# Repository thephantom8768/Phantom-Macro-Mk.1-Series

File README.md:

# Phantom Macro Mk.1 Series

> A modular, snap-together macropad ecosystem with lateral pogo-pin bus interconnects.

Chain modules side-by-side to expand your desktop workflow—from a compact macro-pad into a full fledge keyboard.

---

## 📌 Project Status

- **Hardware:** Series still in-dev
- **Firmware:** Pad is almost complete but I need to built it to measure the adc. Others are still in-dev
- **Interconnect:** Custom edge-mount 8 pin pogo interface.

---

## ⚡ Features

- **Snap & Chain Topology:** Expand your layout horizontally by mating adjacent modules using edge-mounted pogo connectors.
- **Unified Bus Standard:** Standardized power, ground, and communication rails allow any Mk.1-series compatible module to hot-mate with the system.
- **Flexible Layouts:** Mix and match different form factors (numpads, macro clusters, encoder dials) without rerunning separate USB cables to your host machine.

## ⚠️ Build Warnings

> [!WARNING]
> **DIY Soldering Required:** This is a fully self-assembled project. It is not a plug-and-play kit and requires intermediate soldering experience.

* **Double-Sided Assembly:** Depending on the macro-pad, components might need to be soldered onto **both the top and bottom** of the PCB.

## *Mk.1 Series*

<details>
  <summary><b>🔢 Phantom-Macro-Mk.1 Pad (click here)</b></summary>
  
  ### Macro Mk.1 Pad
  
  #### Schematic

#### PCB Layout

4 Layers PCB

<div style="width: max; height: max; overflow: hidden; display: inline-block;">
  
</div>

| Front (1st layer) | Bottom (4th layer) |
| ----------------- | ------------------ |
|  |  |
|  |  |

#### PCB
| Front | Back |
| ----- | ---- |
|  |  |
|  |  |

#### Case

<table>
  <tbody>
    <tr>
      <td width="50%">
        
      </td>
      <td width="50%">
        
      </td>
    </tr>
    <tr>
      <td width="50%">
        
      </td>
      <td width="50%">
        
      </td>
    </tr>
  </tbody>
</table>

</details>

<details>
  <summary><b>🎹 Phantom-Macro-Mk.1 MIDI (click here)</b></summary>
  
  ### Macro Mk.1 MIDI
  
  #### Schematic

  #### PCB Layout 

  2 Layers PCB

  | Front | Back |
  | ----- | ----- |
  |  |  |
  |  |  |

  #### PCB
  | Front | Back |
  | ----- | ---- |
  |  |  |
  |  |  |

</details>

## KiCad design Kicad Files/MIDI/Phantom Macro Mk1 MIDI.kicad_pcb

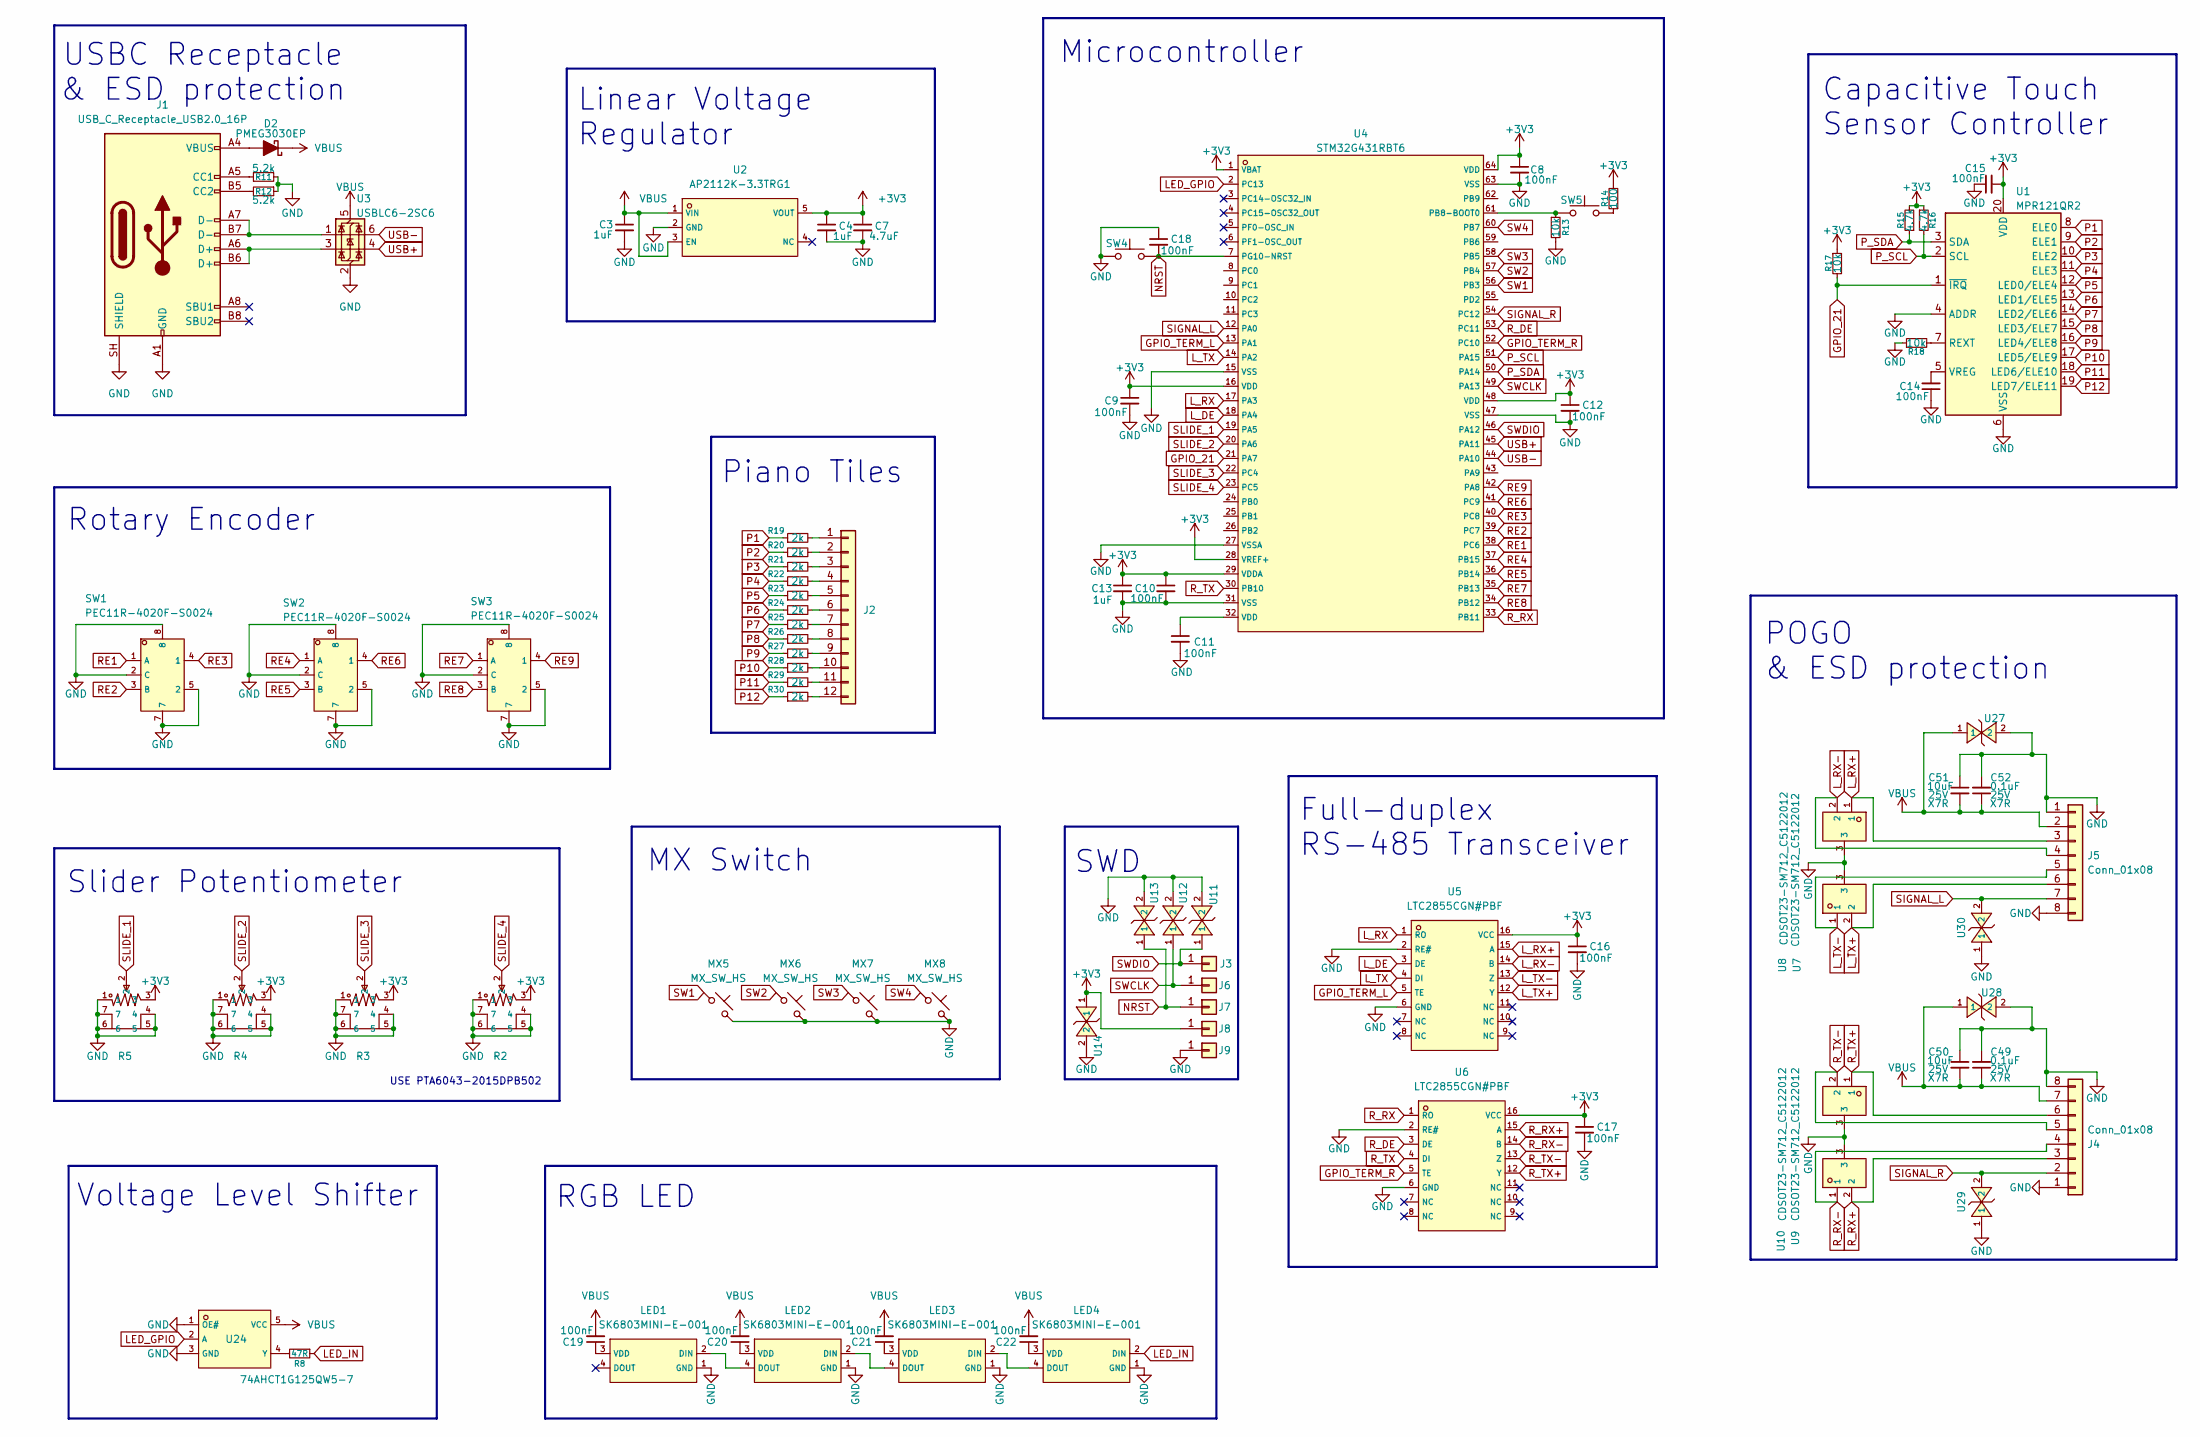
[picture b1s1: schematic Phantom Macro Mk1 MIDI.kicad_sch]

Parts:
C3, C4, C13: 1uF; C_0603_1608Metric_Pad1.08x0.95mm_HandSolder
C7: 4.7uF; C_0805_2012Metric_Pad1.18x1.45mm_HandSolder
C8, C9, C10, C11, C12, C14, C15, C16, C17, C18, C19, C20, C21, C22: 100nF; C_0402_1005Metric_Pad0.74x0.62mm_HandSolder
C49, C52: 0.1uF; C_0805_2012Metric_Pad1.18x1.45mm_HandSolder; Rating 25V
C50, C51: 10uF; C_0805_2012Metric_Pad1.18x1.45mm_HandSolder; Rating 25V
D2: PMEG3030EP; D_SOD-128
J1: USB_C_Receptacle_USB2.0_16P; USB_C_Receptacle_GCT_USB4110
J2: Conn_01x12; 7 key piano tiles
J3, J6, J7, J8, J9: Conn_01x01; PinSocket_1x01_P2.54mm_Vertical
J4, J5: Conn_01x08; PinHeader_1x08_P2.54mm_Horizontal
LED1, LED2, LED3, LED4: SK6803MINI-E-001; C5242955_LED-SMD_4P-L3_2-W2_8_SK6803MINI-E-001; LCSC C5242955
MX5, MX6, MX7, MX8: MX_SW_HS; SW_MX_HS_CPG151101S11_1u
R2, R3, R4, R5: PTA6043-2015DPA103; C17237498_RES-ADJ-TH_PTA6043-XXXX; LCSC C17237498
R8: 47R; R_0402_1005Metric_Pad0.72x0.64mm_HandSolder
R11, R12: 5.2k; R_0402_1005Metric_Pad0.72x0.64mm_HandSolder
R13, R17, R18: 10k; R_0402_1005Metric_Pad0.72x0.64mm_HandSolder
R14: 100; R_0402_1005Metric_Pad0.72x0.64mm_HandSolder
R15, R16: 4.7k; R_0402_1005Metric_Pad0.72x0.64mm_HandSolder
R19, R20, R21, R22, R23, R24, R25, R26, R27, R28, R29, R30: 2k; R_0402_1005Metric_Pad0.72x0.64mm_HandSolder
SW1, SW2, SW3: PEC11R-4020F-S0024; C143788_SW-TH_5P-L12_5-W13_4-P2_50-LS14_5; LCSC C143788
SW4, SW5: SW_Push; SW_SPST_B3U-1000P
U1: MPR121QR2; UQFN-20_3x3mm_P0.4mm
U2: AP2112K-3.3TRG1; C51118_SOT-25-5_L2_9-W1_6-P0_95-LS2_8-BL; LCSC C51118
U3: USBLC6-2SC6; SOT-23-6
U4: STM32G431RBT6; C431633_LQFP-64_L10_0-W10_0-P0_50-LS12_0-BL; LCSC C431633
U5, U6: LTC2855CGN#PBF; C682796_SSOP-16_L4_9-W3_9-P0_64-LS6_0-BL; LCSC C682796
U7, U8, U9, U10: CDSOT23-SM712_C5122012; C5122012_SOT-23-3_L2_9-W1_3-P0_95-LS2_4-BR; LCSC C5122012
U11, U12, U13, U14, U27, U28, U29, U30: TPD1E10B06DPYR; C48260_X1SON-2_L1_0-W0_6-P0_65-BI-1; LCSC C48260
U24: 74AHCT1G125QW5-7; C3755013_SOT-753_L3_1-W1_7-P0_95-LS3_0-BR; LCSC C3755013

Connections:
+3V3: C4.1, C7.1, C8.1, C9.1, C10.1, C12.1, C13.1, C15.2, C16.1, C17.1, J8.1 (Pin_1_1), R2.3, R3.3, R4.3, R5.3, R14.2, R15.2, R16.1, R17.1, U1.20 (VDD), U2.5 (VOUT), U4.1 (VBAT), U4.16 (VDD), U4.28 (VREF+), U4.29 (VDDA), U4.48 (VDD), U4.64 (VDD), U5.16 (VCC), U6.16 (VCC), U14.1
GND: C3.2, C4.2, C7.2, C8.2, C9.2, C10.2, C11.2, C12.2, C13.2, C14.1, C15.1, C16.2, C17.2, C18.1, C49.2, C50.1, C51.1, C52.2, J1.A1 (GND), J1.A12 (GND), J1.B1 (GND), J1.B12 (GND), J1.SH (SHIELD), J4.1, J4.8, J5.1, J5.8, J9.1 (Pin_1_1), LED1.1 (GND), LED2.1 (GND), LED3.1 (GND), LED4.1 (GND), MX5.2, MX6.2, MX7.2, MX8.2, R2.1, R2.4, R2.5, R2.6, R2.7, R3.1, R3.4, R3.5, R3.6, R3.7, R4.1, R4.4, R4.5, R4.6, R4.7, R5.1, R5.4, R5.5, R5.6, R5.7, R11.2, R12.1, R13.2, R18.1, SW1.2 (C), SW1.5 (2), SW1.7, SW1.8, SW2.2 (C), SW2.5 (2), SW2.7, SW2.8, SW3.2 (C), SW3.5 (2), SW3.7, SW3.8, SW4.1, U1.4 (ADDR), U1.6 (VSS), U2.2 (GND), U3.2 (GND), U4.15 (VSS), U4.27 (VSSA), U4.31 (VSS), U4.47 (VSS), U4.63 (VSS), U5.2 (RE#), U5.6 (GND), U6.2 (RE#), U6.6 (GND), U7.3, U8.3, U9.3, U10.3, U11.2, U12.2, U13.2, U14.2, U24.1 (OE#), U24.3 (GND), U27.2, U28.2, U29.1, U30.1
GPIO_21: R17.2, U1.1 (~IRQ), U4.21 (PA7)
GPIO_TERM_L: U4.13 (PA1), U5.5 (TE)
GPIO_TERM_R: U4.52 (PC10), U6.5 (TE)
LED_GPIO: U4.2 (PC13), U24.2 (A)
LED_IN: LED4.2 (DIN), R8.1
L_DE: U4.18 (PA4), U5.3 (DE)
L_RX: U4.17 (PA3), U5.1 (RO)
L_RX+: J5.3, U5.15 (A), U7.1
L_RX-: J5.4, U5.14 (B), U7.2
L_TX: U4.14 (PA2), U5.4 (DI)
L_TX+: J5.6, U5.12 (Y), U8.2
L_TX-: J5.5, U5.13 (Z), U8.1
NRST: C18.2, J7.1 (Pin_1_1), SW4.2, U4.7 (PG10-NRST), U13.1
unnamed: C11.1, U4.32 (VDD)
unnamed: D2.2 (A), J1.A4 (VBUS), J1.A9 (VBUS), J1.B4 (VBUS), J1.B9 (VBUS)
unnamed: J1.A5 (CC1), R11.1
unnamed: J1.B5 (CC2), R12.2
unnamed: J1.A6 (D+), J1.B6 (D+), U3.3 (I/O2)
unnamed: J1.A7 (D-), J1.B7 (D-), U3.1 (I/O1)
unnamed: J2.1, R19.2
unnamed: J2.2, R20.2
unnamed: J2.3, R21.2
unnamed: J2.4, R22.2
unnamed: J2.5, R23.2
unnamed: J2.6, R24.2
unnamed: J2.7, R25.2
unnamed: J2.8, R26.2
unnamed: J2.9, R27.2
unnamed: J2.10, R28.2
unnamed: J2.11, R29.2
unnamed: J2.12, R30.2
unnamed: LED1.2 (DIN), LED2.4 (DOUT)
unnamed: C19.1, LED1.3 (VDD)
unnamed: LED2.2 (DIN), LED3.4 (DOUT)
unnamed: C20.1, LED2.3 (VDD)
unnamed: LED3.2 (DIN), LED4.4 (DOUT)
unnamed: C21.1, LED3.3 (VDD)
unnamed: C22.1, LED4.3 (VDD)
unnamed: R14.1, SW5.2
unnamed: R18.2, U1.7 (REXT)
unnamed: C14.2, U1.5 (VREG)
unnamed: R13.1, SW5.1, U4.61 (PB8-BOOT0)
unnamed: R8.2, U24.4 (Y)
P1: R19.1, U1.8 (ELE0)
P2: R20.1, U1.9 (ELE1)
P3: R21.1, U1.10 (ELE2)
P4: R22.1, U1.11 (ELE3)
P5: R23.1, U1.12 (LED0/ELE4)
P6: R24.1, U1.13 (LED1/ELE5)
P7: R25.1, U1.14 (LED2/ELE6)
P8: R26.1, U1.15 (LED3/ELE7)
P9: R27.1, U1.16 (LED4/ELE8)
P10: R28.1, U1.17 (LED5/ELE9)
P11: R29.1, U1.18 (LED6/ELE10)
P12: R30.1, U1.19 (LED7/ELE11)
P_SCL: R16.2, U1.2 (SCL), U4.51 (PA15)
P_SDA: R15.1, U1.3 (SDA), U4.50 (PA14)
RE1: SW1.1 (A), U4.38 (PC6)
RE2: SW1.3 (B), U4.39 (PC7)
RE3: SW1.4 (1), U4.40 (PC8)
RE4: SW2.1 (A), U4.37 (PB15)
RE5: SW2.3 (B), U4.36 (PB14)
RE6: SW2.4 (1), U4.41 (PC9)
RE7: SW3.1 (A), U4.35 (PB13)
RE8: SW3.3 (B), U4.34 (PB12)
RE9: SW3.4 (1), U4.42 (PA8)
R_DE: U4.53 (PC11), U6.3 (DE)
R_RX: U4.33 (PB11), U6.1 (RO)
R_RX+: J4.3, U6.15 (A), U10.2
R_RX-: J4.4, U6.14 (B), U10.1
R_TX: U4.30 (PB10), U6.4 (DI)
R_TX+: J4.6, U6.12 (Y), U9.1
R_TX-: J4.5, U6.13 (Z), U9.2
SIGNAL_L: J5.7, U4.12 (PA0), U30.2
SIGNAL_R: J4.2, U4.54 (PC12), U29.2
SLIDE_1: R5.2, U4.19 (PA5)
SLIDE_2: R4.2, U4.20 (PA6)
SLIDE_3: R3.2, U4.22 (PC4)
SLIDE_4: R2.2, U4.23 (PC5)
SW1: MX5.1, U4.56 (PB3)
SW2: MX6.1, U4.57 (PB4)
SW3: MX7.1, U4.58 (PB5)
SW4: MX8.1, U4.60 (PB7)
SWCLK: J6.1 (Pin_1_1), U4.49 (PA13), U12.1
SWDIO: J3.1 (Pin_1_1), U4.46 (PA12), U11.1
USB+: U3.4 (I/O2), U4.45 (PA11)
USB-: U3.6 (I/O1), U4.44 (PA10)
VBUS: C3.1, C19.2, C20.2, C21.2, C22.2, C49.1, C50.2, C51.2, C52.1, D2.1 (K), J4.7, J5.2, U2.1 (VIN), U2.3 (EN), U3.5 (VBUS), U24.5 (VCC), U27.1, U28.1

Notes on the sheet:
Voltage Level Shifter
Full-duplex RS-485 Transceiver
MX Switch
Slider Potentiometer
Piano Tiles
USE PTA6043-2015DPB502
Microcontroller
POGO & ESD protection
Capacitive Touch Sensor Controller
SWD
RGB LED
Rotary Encoder
Linear Voltage Regulator
USBC Receptacle & ESD protection

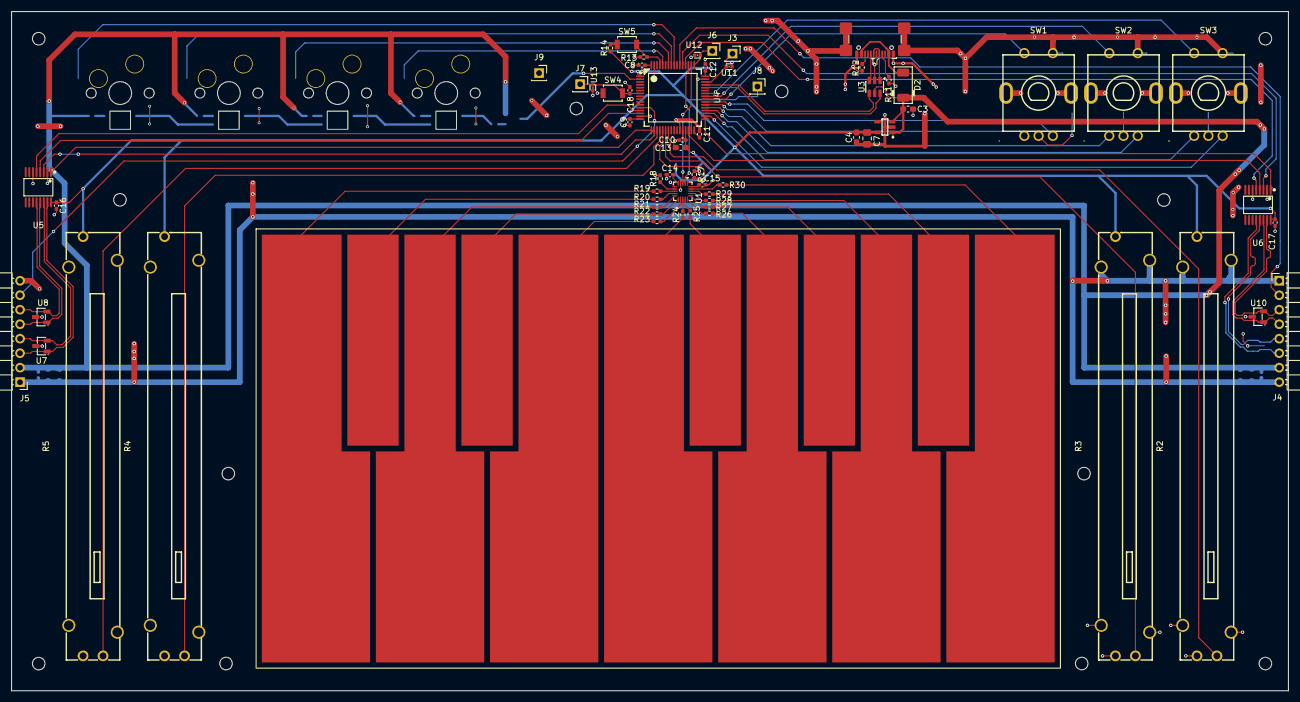
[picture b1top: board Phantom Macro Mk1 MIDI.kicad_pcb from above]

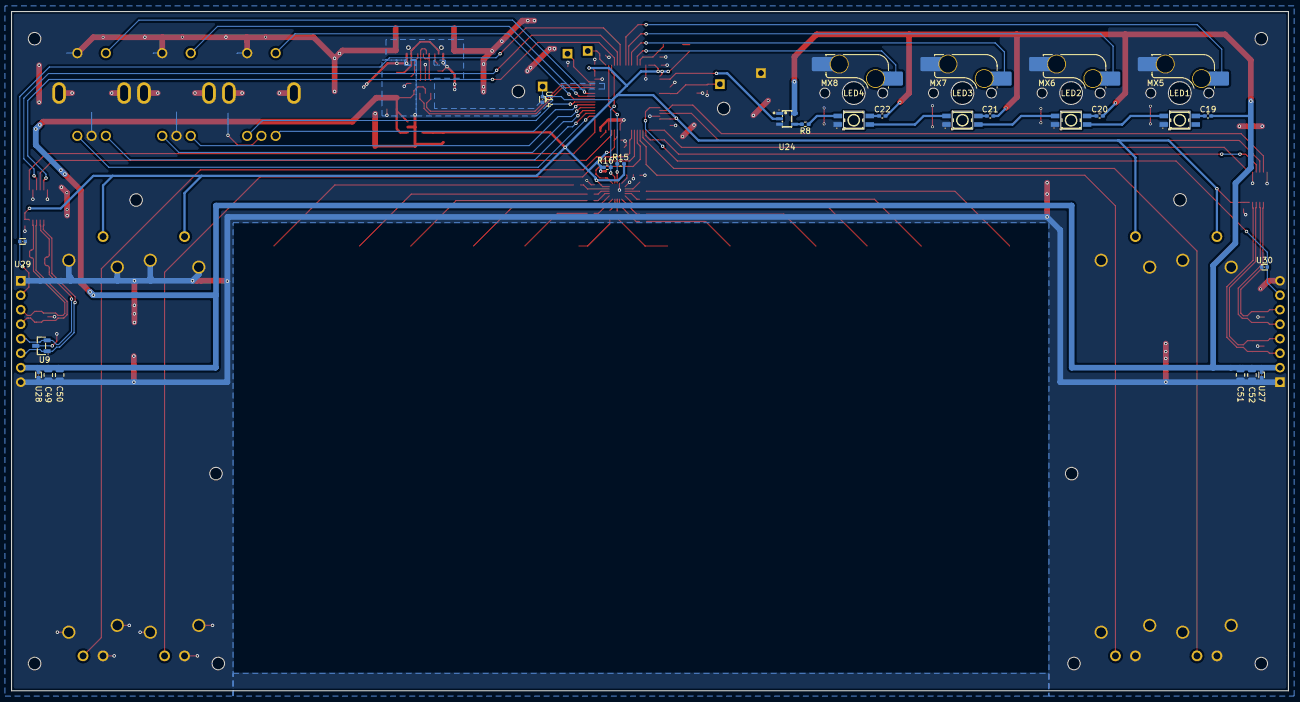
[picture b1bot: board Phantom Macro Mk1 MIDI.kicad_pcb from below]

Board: 2 copper layers, 223.8 x 119.1 mm, 89 parts (26 on the bottom side), 90 nets.

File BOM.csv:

Item,Qty,Supplier,Cost/item,Total Cost,link
1uF,18,TaoBao,$0.00,$0.00,https://item.taobao.com/item.htm?from=cart&id=630712731066&m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
0.1uF,16,TaoBao,$0.00,$0.00,https://item.taobao.com/item.htm?from=cart&id=731471380840&m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
100nF,8,TaoBao,$0.00,$0.00,https://item.taobao.com/item.htm?abbucket=0&id=733879274781&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
10uF,2,TaoBao,$0.00,$0.00,https://item.taobao.com/item.htm?abbucket=0&id=977236759812&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
0.1uF,2,TaoBao,$0.00,$0.00,https://item.taobao.com/item.htm?abbucket=0&id=730748325366&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
PMEG3030EP,1,TaoBao,$0.36,$0.36,https://item.taobao.com/item.htm?abbucket=20&id=694578569169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
USBLC6-2SC6,1,TaoBao,$0.23,$0.23,https://item.taobao.com/item.htm?id=763430084934&mi_id=0000e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
USB_C_Receptacle_USB2.0_16P,1,TaoBao,$0.08,$0.08,https://item.taobao.com/item.htm?id=591211481748&mi_id=0000r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
Conn_01x08,2,TaoBao,$1.04,$2.08,https://item.taobao.com/item.htm?ali_refid=a3_mm_12852562_17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
SK6803MINI-E-001,16,TaoBao,$0.04,$0.64,https://item.taobao.com/item.htm?abbucket=20&id=107449241269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
5.1k,2,TaoBao,$0.00,$0.00,https://item.taobao.com/item.htm?id=525633713781&mi_id=0000g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
47R,1,TaoBao,$0.00,$0.00,https://item.taobao.com/item.htm?id=525633713781&mi_id=0000g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
10k,1,TaoBao,$0.00,$0.00,https://item.taobao.com/item.htm?id=525633713781&mi_id=0000g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
PEC11R-4020F-S0024,1,TaoBao,$3.54,$3.54,https://item.taobao.com/item.htm?abbucket=20&id=755153501399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
SPST B3U-1000P,2,TaoBao,$0.10,$0.20,https://item.taobao.com/item.htm?abbucket=20&id=106190013432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
SW_MX_HE,16,Milktooth,$0.85,$13.60,https://milktooth.com/products/dove-he
AP2112K-3.3TRG1,1,TaoBao,$0.55,$0.55,https://intl.taobao.com/sk/_b.OcKv5a
CD74HC4067SM96,2,TaoBao,$0.35,$0.70,https://item.taobao.com/item.htm?id=659268510241&mi_id=00007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
74AHCT1G125QW5-7,1,TaoBao,$0.31,$0.31,https://item.taobao.com/item.htm?id=581190029859&mi_id=0000C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
STM32G431CBT6,1,TaoBao,$3.67,$3.67,https://item.taobao.com/item.htm?id=662218011027&mi_id=0000x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
LTC2855CGN#PBF,2,AliXpress,$8.44,$16.88,https://a.aliexpress.com/_c40x90oj
CDSOT23-SM712_C5122012,4,TaoBao,$0.05,$0.20,https://detail.tmall.com/item.htm?from=cart&id=903941269382&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
TPD1E10B06DPYR,4,TaoBao,$0.08,$0.32,https://item.taobao.com/item.htm?id=594637912684&mi_id=0000W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
DRV5055,16,TaoBao,$0.94,$15.04,https://detail.tmall.com/item.htm?from=cart&id=660549060773&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
PCB,1,JLCPCB,$29.30,$29.30,https://JLCPCB.com
Estimated total shipping,1,,,$7.13,

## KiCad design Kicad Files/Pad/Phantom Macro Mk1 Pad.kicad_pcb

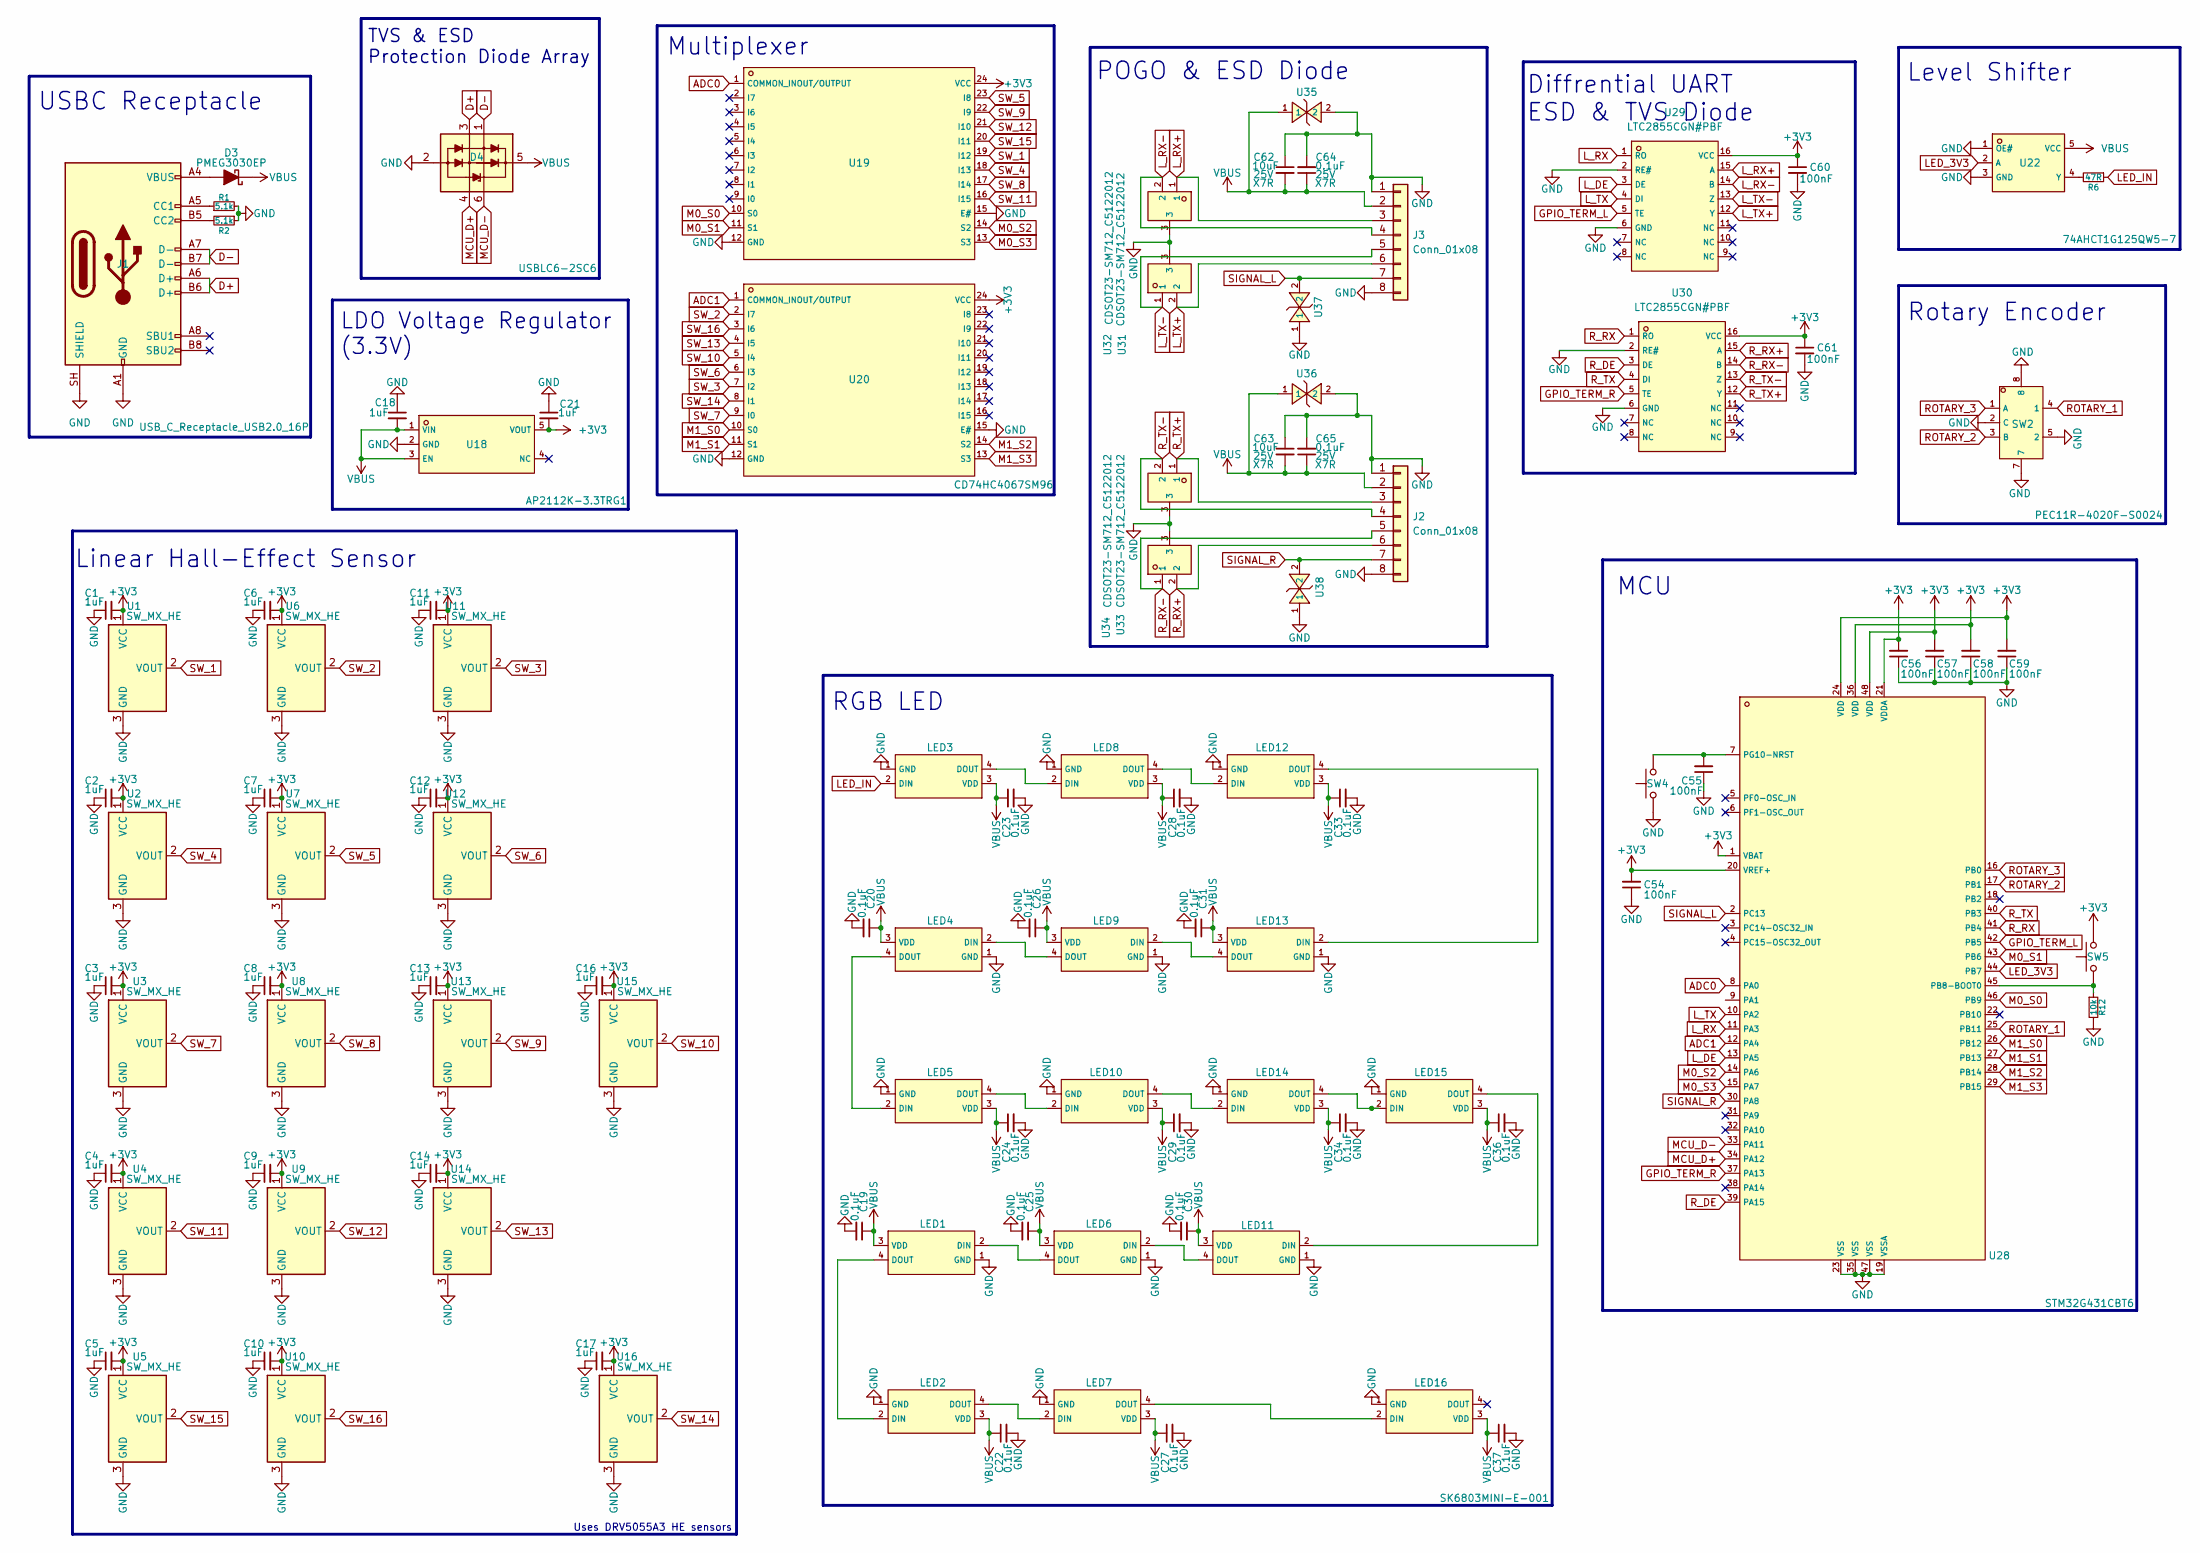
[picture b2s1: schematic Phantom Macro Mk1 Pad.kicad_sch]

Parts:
C1, C2, C3, C4, C5, C6, C7, C8, C9, C10, C11, C12, C13, C14, C16, C17, C18, C21: 1uF; C_0603_1608Metric_Pad1.08x0.95mm_HandSolder
C19, C20, C22, C23, C24, C25, C26, C27, C28, C29, C30, C31, C33, C34, C36, C37: 0.1uF; C_0603_1608Metric_Pad1.08x0.95mm_HandSolder
C54, C55, C56, C57, C58, C59, C60, C61: 100nF; C_0402_1005Metric_Pad0.74x0.62mm_HandSolder
C62, C63: 10uF; C_0805_2012Metric_Pad1.18x1.45mm_HandSolder; Rating 25V
C64, C65: 0.1uF; C_0805_2012Metric_Pad1.18x1.45mm_HandSolder; Rating 25V
D3: PMEG3030EP; D_SOD-128
D4: USBLC6-2SC6; SOT-23-6
J1: USB_C_Receptacle_USB2.0_16P; USB_C_Receptacle_GCT_USB4110
J2, J3: Conn_01x08; PinHeader_1x08_P2.54mm_Horizontal
LED1, LED2, LED3, LED4, LED5, LED6, LED7, LED8, LED9, LED10, LED11, LED12, LED13, LED14, LED15, LED16: SK6803MINI-E-001; C5242955_LED-SMD_4P-L3_2-W2_8_SK6803MINI-E-001; LCSC C5242955
R1, R2: 5.1k; R_0402_1005Metric_Pad0.72x0.64mm_HandSolder
R6: 47R; R_0402_1005Metric_Pad0.72x0.64mm_HandSolder
R12: 10k; R_0402_1005Metric_Pad0.72x0.64mm_HandSolder
SW2: PEC11R-4020F-S0024; C143788_SW-TH_5P-L12_5-W13_4-P2_50-LS14_5; LCSC C143788
SW4, SW5: SW_Push; SW_SPST_B3U-1000P
U1, U2, U3, U4, U5, U6, U7, U8, U9, U10, U11, U12, U13, U14, U15, U16: SW_MX_HE; Haimu Dove H V2
U18: AP2112K-3.3TRG1; C51118_SOT-25-5_L2_9-W1_6-P0_95-LS2_8-BL; LCSC C51118
U19, U20: CD74HC4067SM96; C98457_SSOP-24_L8_1-W5_3-P0_65-LS7_8-BL; LCSC C98457
U22: 74AHCT1G125QW5-7; C3755013_SOT-753_L3_1-W1_7-P0_95-LS3_0-BR; LCSC C3755013
U28: STM32G431CBT6; C529355_LQFP-48_L7_0-W7_0-P0_50-LS9_0-BL; LCSC C529355
U29, U30: LTC2855CGN#PBF; C682796_SSOP-16_L4_9-W3_9-P0_64-LS6_0-BL; LCSC C682796
U31, U32, U33, U34: CDSOT23-SM712_C5122012; C5122012_SOT-23-3_L2_9-W1_3-P0_95-LS2_4-BR; LCSC C5122012
U35, U36, U37, U38: TPD1E10B06DPYR; C48260_X1SON-2_L1_0-W0_6-P0_65-BI-1; LCSC C48260

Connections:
+3V3: C1.2, C2.2, C3.2, C4.2, C5.2, C6.2, C7.2, C8.2, C9.2, C10.2, C11.2, C12.2, C13.2, C14.2, C16.2, C17.2, C21.2, C54.2, C56.2, C57.2, C58.2, C59.2, C60.1, C61.1, SW5.2, U1.1 (VCC), U2.1 (VCC), U3.1 (VCC), U4.1 (VCC), U5.1 (VCC), U6.1 (VCC), U7.1 (VCC), U8.1 (VCC), U9.1 (VCC), U10.1 (VCC), U11.1 (VCC), U12.1 (VCC), U13.1 (VCC), U14.1 (VCC), U15.1 (VCC), U16.1 (VCC), U18.5 (VOUT), U19.24 (VCC), U20.24 (VCC), U28.1 (VBAT), U28.20 (VREF+), U28.21 (VDDA), U28.24 (VDD), U28.36 (VDD), U28.48 (VDD), U29.16 (VCC), U30.16 (VCC)
ADC0: U19.1 (COMMON_INOUT/OUTPUT), U28.8 (PA0)
ADC1: U20.1 (COMMON_INOUT/OUTPUT), U28.12 (PA4)
D+: D4.3 (L2), J1.A6 (D+), J1.B6 (D+)
D-: D4.1 (L1), J1.A7 (D-), J1.B7 (D-)
GND: C1.1, C2.1, C3.1, C4.1, C5.1, C6.1, C7.1, C8.1, C9.1, C10.1, C11.1, C12.1, C13.1, C14.1, C16.1, C17.1, C18.1, C19.2, C20.2, C21.1, C22.2, C23.2, C24.2, C25.2, C26.2, C27.2, C28.2, C29.2, C30.2, C31.2, C33.2, C34.2, C36.2, C37.2, C54.1, C55.1, C56.1, C57.1, C58.1, C59.1, C60.2, C61.2, C62.1, C63.1, C64.2, C65.2, D4.2 (VN), J1.A1 (GND), J1.A12 (GND), J1.B1 (GND), J1.B12 (GND), J1.SH (SHIELD), J2.1, J2.8, J3.1, J3.8, LED1.1 (GND), LED2.1 (GND), LED3.1 (GND), LED4.1 (GND), LED5.1 (GND), LED6.1 (GND), LED7.1 (GND), LED8.1 (GND), LED9.1 (GND), LED10.1 (GND), LED11.1 (GND), LED12.1 (GND), LED13.1 (GND), LED14.1 (GND), LED15.1 (GND), LED16.1 (GND), R1.2, R2.1, R12.2, SW2.2 (C), SW2.5 (2), SW2.7, SW2.8, SW4.1, U1.3 (GND), U2.3 (GND), U3.3 (GND), U4.3 (GND), U5.3 (GND), U6.3 (GND), U7.3 (GND), U8.3 (GND), U9.3 (GND), U10.3 (GND), U11.3 (GND), U12.3 (GND), U13.3 (GND), U14.3 (GND), U15.3 (GND), U16.3 (GND), U18.2 (GND), U19.12 (GND), U19.15 (E#), U20.12 (GND), U20.15 (E#), U22.1 (OE#), U22.3 (GND), U28.19 (VSSA), U28.23 (VSS), U28.35 (VSS), U28.47 (VSS), U29.2 (RE#), U29.6 (GND), U30.2 (RE#), U30.6 (GND), U31.3, U32.3, U33.3, U34.3, U35.2, U36.2, U37.1, U38.1
GPIO_TERM_L: U28.42 (PB5), U29.5 (TE)
GPIO_TERM_R: U28.37 (PA13), U30.5 (TE)
LED_3V3: U22.2 (A), U28.44 (PB7)
LED_IN: LED3.2 (DIN), R6.1
L_DE: U28.13 (PA5), U29.3 (DE)
L_RX: U28.11 (PA3), U29.1 (RO)
L_RX+: J3.3, U29.15 (A), U31.1
L_RX-: J3.4, U29.14 (B), U31.2
L_TX: U28.10 (PA2), U29.4 (DI)
L_TX+: J3.6, U29.12 (Y), U32.2
L_TX-: J3.5, U29.13 (Z), U32.1
M0_S0: U19.10 (S0), U28.46 (PB9)
M0_S1: U19.11 (S1), U28.43 (PB6)
M0_S2: U19.14 (S2), U28.14 (PA6)
M0_S3: U19.13 (S3), U28.15 (PA7)
M1_S0: U20.10 (S0), U28.26 (PB12)
M1_S1: U20.11 (S1), U28.27 (PB13)
M1_S2: U20.14 (S2), U28.28 (PB14)
M1_S3: U20.13 (S3), U28.29 (PB15)
MCU_D+: D4.4 (L2), U28.34 (PA12)
MCU_D-: D4.6 (L1), U28.33 (PA11)
unnamed: D3.2 (A), J1.A4 (VBUS), J1.A9 (VBUS), J1.B4 (VBUS), J1.B9 (VBUS)
unnamed: J1.A5 (CC1), R1.1
unnamed: J1.B5 (CC2), R2.2
unnamed: LED1.2 (DIN), LED6.4 (DOUT)
unnamed: LED1.4 (DOUT), LED2.2 (DIN)
unnamed: LED2.4 (DOUT), LED7.2 (DIN)
unnamed: LED3.4 (DOUT), LED8.2 (DIN)
unnamed: LED4.2 (DIN), LED9.4 (DOUT)
unnamed: LED4.4 (DOUT), LED5.2 (DIN)
unnamed: LED5.4 (DOUT), LED10.2 (DIN)
unnamed: LED10.4 (DOUT), LED14.2 (DIN)
unnamed: LED11.2 (DIN), LED15.4 (DOUT)
unnamed: LED6.2 (DIN), LED11.4 (DOUT)
unnamed: LED8.4 (DOUT), LED12.2 (DIN)
unnamed: LED12.4 (DOUT), LED13.2 (DIN)
unnamed: LED9.2 (DIN), LED13.4 (DOUT)
unnamed: LED14.4 (DOUT), LED15.2 (DIN)
unnamed: LED7.4 (DOUT), LED16.2 (DIN)
unnamed: R6.2, U22.4 (Y)
unnamed: R12.1, SW5.1, U28.45 (PB8-BOOT0)
unnamed: C55.2, SW4.2, U28.7 (PG10-NRST)
ROTARY_1: SW2.4 (1), U28.25 (PB11)
ROTARY_2: SW2.3 (B), U28.17 (PB1)
ROTARY_3: SW2.1 (A), U28.16 (PB0)
R_DE: U28.39 (PA15), U30.3 (DE)
R_RX: U28.41 (PB4), U30.1 (RO)
R_RX+: J2.6, U30.15 (A), U34.2
R_RX-: J2.5, U30.14 (B), U34.1
R_TX: U28.40 (PB3), U30.4 (DI)
R_TX+: J2.3, U30.12 (Y), U33.1
R_TX-: J2.4, U30.13 (Z), U33.2
SIGNAL_L: J3.7, U28.2 (PC13), U37.2
SIGNAL_R: J2.7, U28.30 (PA8), U38.2
SW_1: U1.2 (VOUT), U19.19 (I12)
SW_2: U6.2 (VOUT), U20.2 (I7)
SW_3: U11.2 (VOUT), U20.7 (I2)
SW_4: U2.2 (VOUT), U19.18 (I13)
SW_5: U7.2 (VOUT), U19.23 (I8)
SW_6: U12.2 (VOUT), U20.6 (I3)
SW_7: U3.2 (VOUT), U20.9 (I0)
SW_8: U8.2 (VOUT), U19.17 (I14)
SW_9: U13.2 (VOUT), U19.22 (I9)
SW_10: U15.2 (VOUT), U20.5 (I4)
SW_11: U4.2 (VOUT), U19.16 (I15)
SW_12: U9.2 (VOUT), U19.21 (I10)
SW_13: U14.2 (VOUT), U20.4 (I5)
SW_14: U16.2 (VOUT), U20.8 (I1)
SW_15: U5.2 (VOUT), U19.20 (I11)
SW_16: U10.2 (VOUT), U20.3 (I6)
VBUS: C18.2, C19.1, C20.1, C22.1, C23.1, C24.1, C25.1, C26.1, C27.1, C28.1, C29.1, C30.1, C31.1, C33.1, C34.1, C36.1, C37.1, C62.2, C63.2, C64.1, C65.1, D3.1 (K), D4.5 (VP), J2.2, J3.2, LED1.3 (VDD), LED2.3 (VDD), LED3.3 (VDD), LED4.3 (VDD), LED5.3 (VDD), LED6.3 (VDD), LED7.3 (VDD), LED8.3 (VDD), LED9.3 (VDD), LED10.3 (VDD), LED11.3 (VDD), LED12.3 (VDD), LED13.3 (VDD), LED14.3 (VDD), LED15.3 (VDD), LED16.3 (VDD), U18.1 (VIN), U18.3 (EN), U22.5 (VCC), U35.1, U36.1

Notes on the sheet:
LDO Voltage Regulator (3.3V)
RGB LED
Multiplexer
Level Shifter
MCU
Rotary Encoder
TVS & ESD Protection Diode Array
Uses DRV5055A3 HE sensors
Linear Hall-Effect Sensor
POGO & ESD Diode
Diffrential UART ESD & TVS Diode
USBC Receptacle

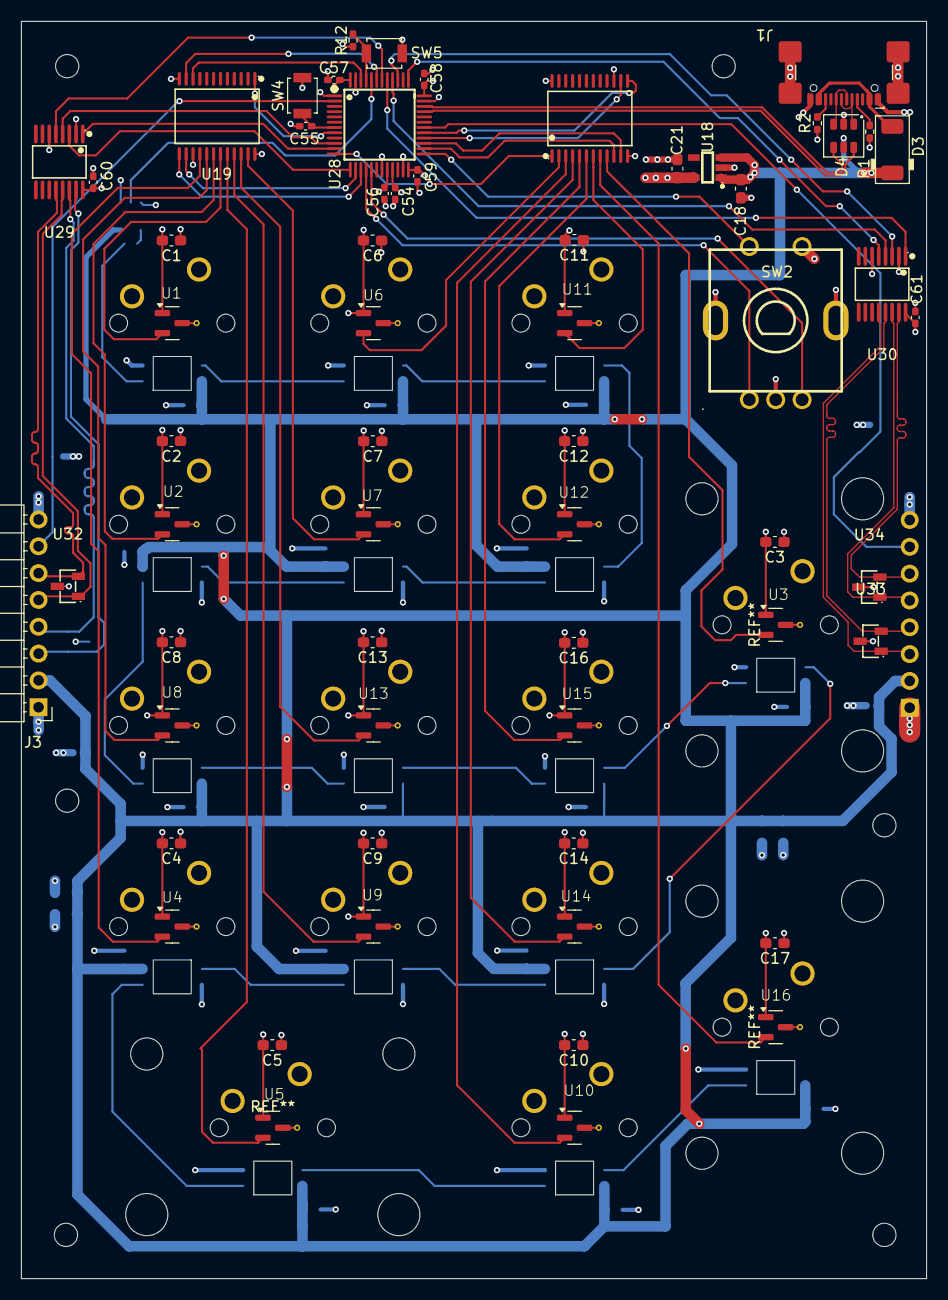
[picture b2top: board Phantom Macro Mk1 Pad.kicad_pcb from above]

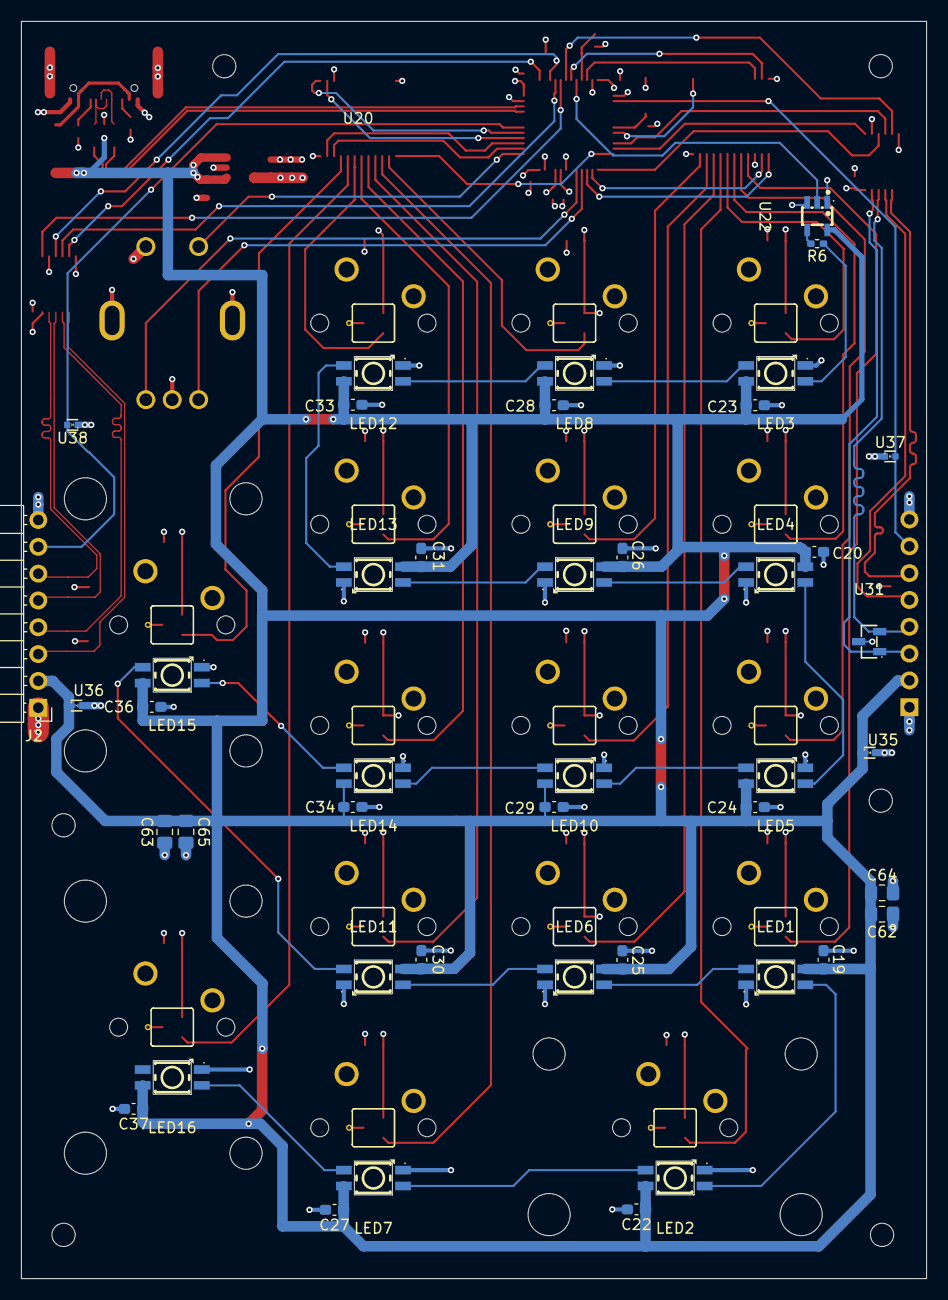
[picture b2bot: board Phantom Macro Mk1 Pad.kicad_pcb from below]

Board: 4 copper layers, 85.7 x 119.1 mm, 105 parts (44 on the bottom side), 77 nets.
